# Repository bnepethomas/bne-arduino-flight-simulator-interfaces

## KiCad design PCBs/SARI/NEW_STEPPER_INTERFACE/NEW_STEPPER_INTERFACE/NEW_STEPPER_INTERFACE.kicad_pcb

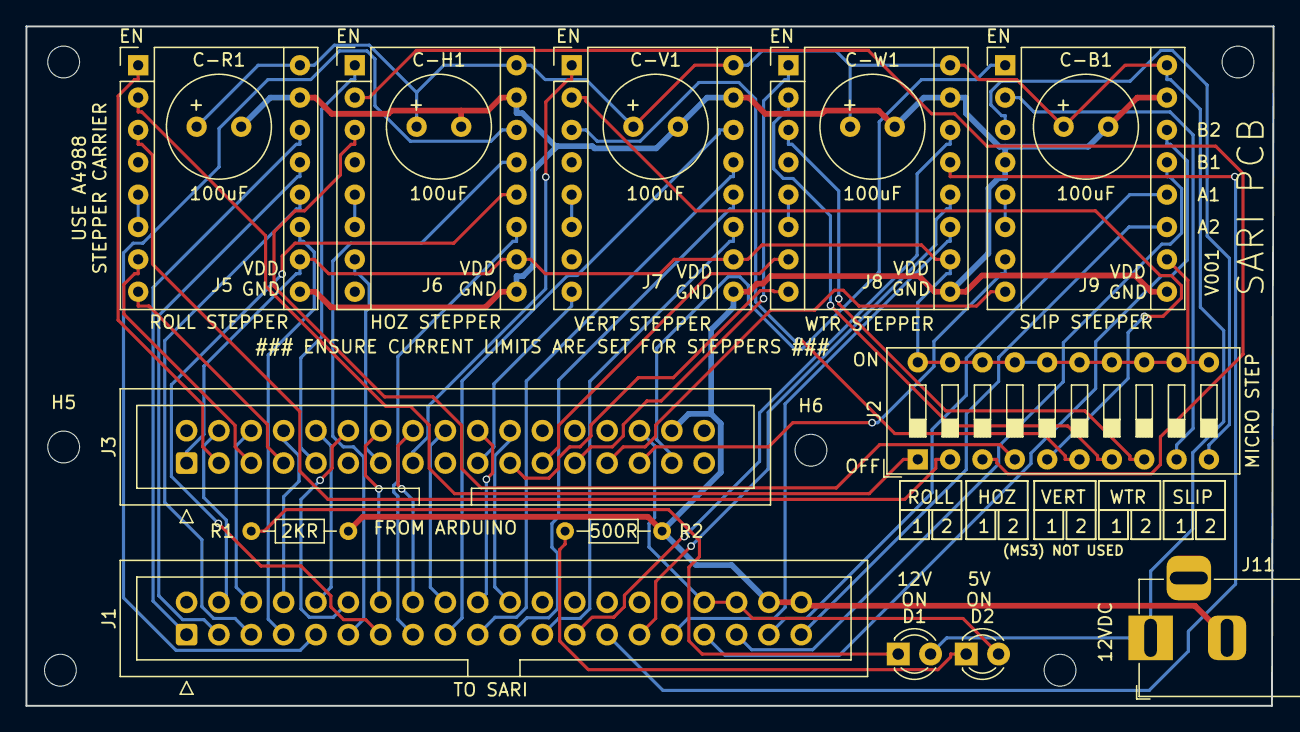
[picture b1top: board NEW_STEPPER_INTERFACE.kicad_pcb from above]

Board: 2 copper layers, 97.9 x 53.3 mm, 24 parts (0 on the bottom side), 64 nets.

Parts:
C-B1: 100uF; C_Radial_D8.0mm_H7.0mm_P3.50mm
C-H1: 100uF; C_Radial_D8.0mm_H7.0mm_P3.50mm
C-R1: 100uF; C_Radial_D8.0mm_H7.0mm_P3.50mm
C-V1: 100uF; C_Radial_D8.0mm_H7.0mm_P3.50mm
C-W1: 100uF; C_Radial_D8.0mm_H7.0mm_P3.50mm
D1, D2: LED; LED_D3.0mm
H1: H1; MountingHole_2.5mm
H2: H2; MountingHole_2.5mm
H3: H3; MountingHole_2.5mm
H4, H5, H6: H4; MountingHole_2.5mm
J1: TO SARI; IDC-Header_2x20_P2.54mm_Vertical
J2: MICRO STEP; SW_DIP_SPSTx10_Slide_9.78x27.58mm_W7.62mm_P2.54mm
J3: FROM ARDUINO; IDC-Header_2x17_P2.54mm_Vertical
J5: ROLL STEPPER; Pololu_Breakout-16_15.2x20.3mm
J6: HOZ STEPPER; Pololu_Breakout-16_15.2x20.3mm
J7: VERT STEPPER; Pololu_Breakout-16_15.2x20.3mm
J8: WTR STEPPER; Pololu_Breakout-16_15.2x20.3mm
J9: SLIP STEPPER; Pololu_Breakout-16_15.2x20.3mm
J11: STEPPER IN 12-20VDC; BarrelJack_Horizontal
R1, R2: R; R_Axial_DIN0204_L3.6mm_D1.6mm_P7.62mm_Horizontal

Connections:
/5VDC: D2.2 (A), J1.34, J1.36, J3.30
/BALL_1A: J1.35, J9.13
/BALL_1B: J1.33, J9.14
/BALL_2A: J1.37, J9.12
/BALL_2B: J1.39, J9.11
/BALL_DIR: J3.27, J9.8
/BALL_EN: J3.31, J9.1
/BALL_MS1: J2.9, J9.2
/BALL_MS2: J2.10, J9.3
/BALL_STEP: J3.29, J9.7
/BALL_STEP_V+: C-B1.1, C-H1.1, C-R1.1, C-V1.1, C-W1.1, D1.2 (A), J5.16, J6.16, J7.16, J8.16, J9.16, J11.1
/ENCODER_A: J1.16, J3.16
/ENCODER_B: J1.18, J3.18
/ENCODER_PUSH: J1.20, J3.20
/HOZ_1A: J1.11, J6.13
/HOZ_1B: J1.9, J6.14
/HOZ_2A: J1.13, J6.12
/HOZ_2B: J1.15, J6.11
/HOZ_EN: J3.9, J6.1
/HOZ_MS1: J2.3, J6.2
/HOZ_MS2: J2.4, J6.3
/HOZ_STEP: J3.13, J6.7
/LED_DATA_IN: J1.12, J3.12
/LED_DATA_OUT: J1.14, J3.14
/ROLL_1A: J1.3, J5.13
/ROLL_1B: J1.1, J5.14
/ROLL_2A: J1.5, J5.12
/ROLL_2B: J1.7, J5.11
/ROLL_DIR: J3.7, J5.8
/ROLL_EN: J3.3, J5.1
/ROLL_MS1: J2.1, J5.2
/ROLL_MS2: J2.2, J5.3
/ROLL_STEP: J3.5, J5.7
/SERVO_FLAG: J1.10, J3.10
/SERVO_PITCH: J1.6, J3.6
/SERVO_RATE: J1.8, J3.8
/TEST_PUSH: J1.22, J3.22
/VDD: J2.11, J2.12, J2.13, J2.14, J2.15, J2.16, J2.17, J2.18, J2.19, J2.20, J3.1, J5.10, J6.10, J7.10, J8.10, J9.10
/VER_1A: J1.19, J7.13
/VER_1B: J1.17, J7.14
/VER_2A: J1.21, J7.12
/VER_2B: J1.23, J7.11
/VER_DIR: J3.19, J7.8
/VER_EN: J3.15, J7.1
/VER_MS1: J2.5, J7.2
/VER_MS2: J2.6, J7.3
/WL_1A: J1.27, J8.13
/WL_1B: J1.25, J8.14
/WL_2A: J1.29, J8.12
/WL_2B: J1.31, J8.11
/WL_DIR: J3.21, J8.8
/WL_EN: J3.25, J8.1
/WL_MS1: J2.7, J8.2
/WL_MS2: J2.8, J8.3
/WL_STEP: J3.23, J8.7
/ZERO_IR: J1.4, J3.4
GNDD: C-B1.2, C-H1.2, C-R1.2, C-V1.2, C-W1.2, J1.38, J1.40, J3.32, J5.9, J5.15, J6.9, J6.15, J7.9, J7.15, J8.9, J8.15, J9.4, J9.9, J9.15, J11.2, R1.1, R2.1
unnamed: D1.1 (K), R1.2
unnamed: D2.1 (K), R2.2
unnamed: J5.5, J5.6
unnamed: J6.5, J6.6
unnamed: J7.5, J7.6
unnamed: J8.5, J8.6
unnamed: J9.5, J9.6

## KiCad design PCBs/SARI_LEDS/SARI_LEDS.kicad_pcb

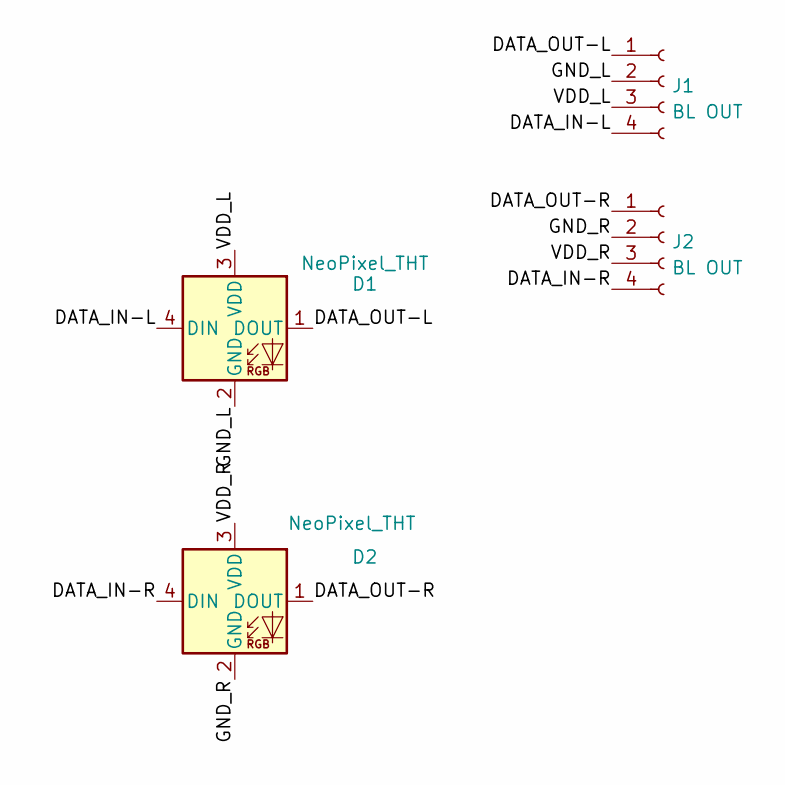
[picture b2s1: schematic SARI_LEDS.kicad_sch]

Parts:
D1, D2: NeoPixel_THT; LED_D5.0mm-4_RGB
J1, J2: BL OUT; PinHeader_1x04_P1.27mm_Vertical

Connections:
/DATA_IN-L: D1.4 (DIN), J1.4
/DATA_IN-R: D2.4 (DIN), J2.4
/DATA_OUT-L: D1.1 (DOUT), J1.1
/DATA_OUT-R: D2.1 (DOUT), J2.1
/GND_L: D1.2 (GND), J1.2
/GND_R: D2.2 (GND), J2.2
/VDD_L: D1.3 (VDD), J1.3
/VDD_R: D2.3 (VDD), J2.3

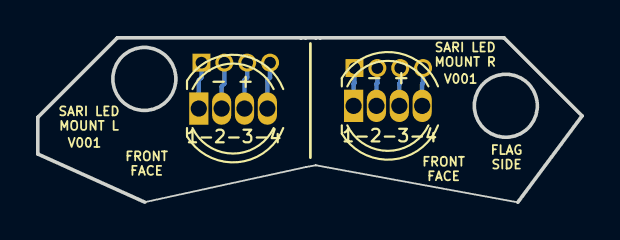
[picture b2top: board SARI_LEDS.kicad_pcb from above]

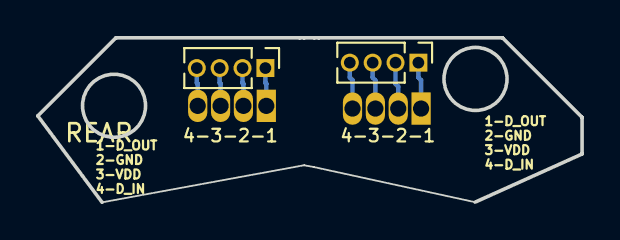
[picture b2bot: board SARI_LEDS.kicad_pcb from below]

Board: 2 copper layers, 30.2 x 9.1 mm, 4 parts (2 on the bottom side), 8 nets.

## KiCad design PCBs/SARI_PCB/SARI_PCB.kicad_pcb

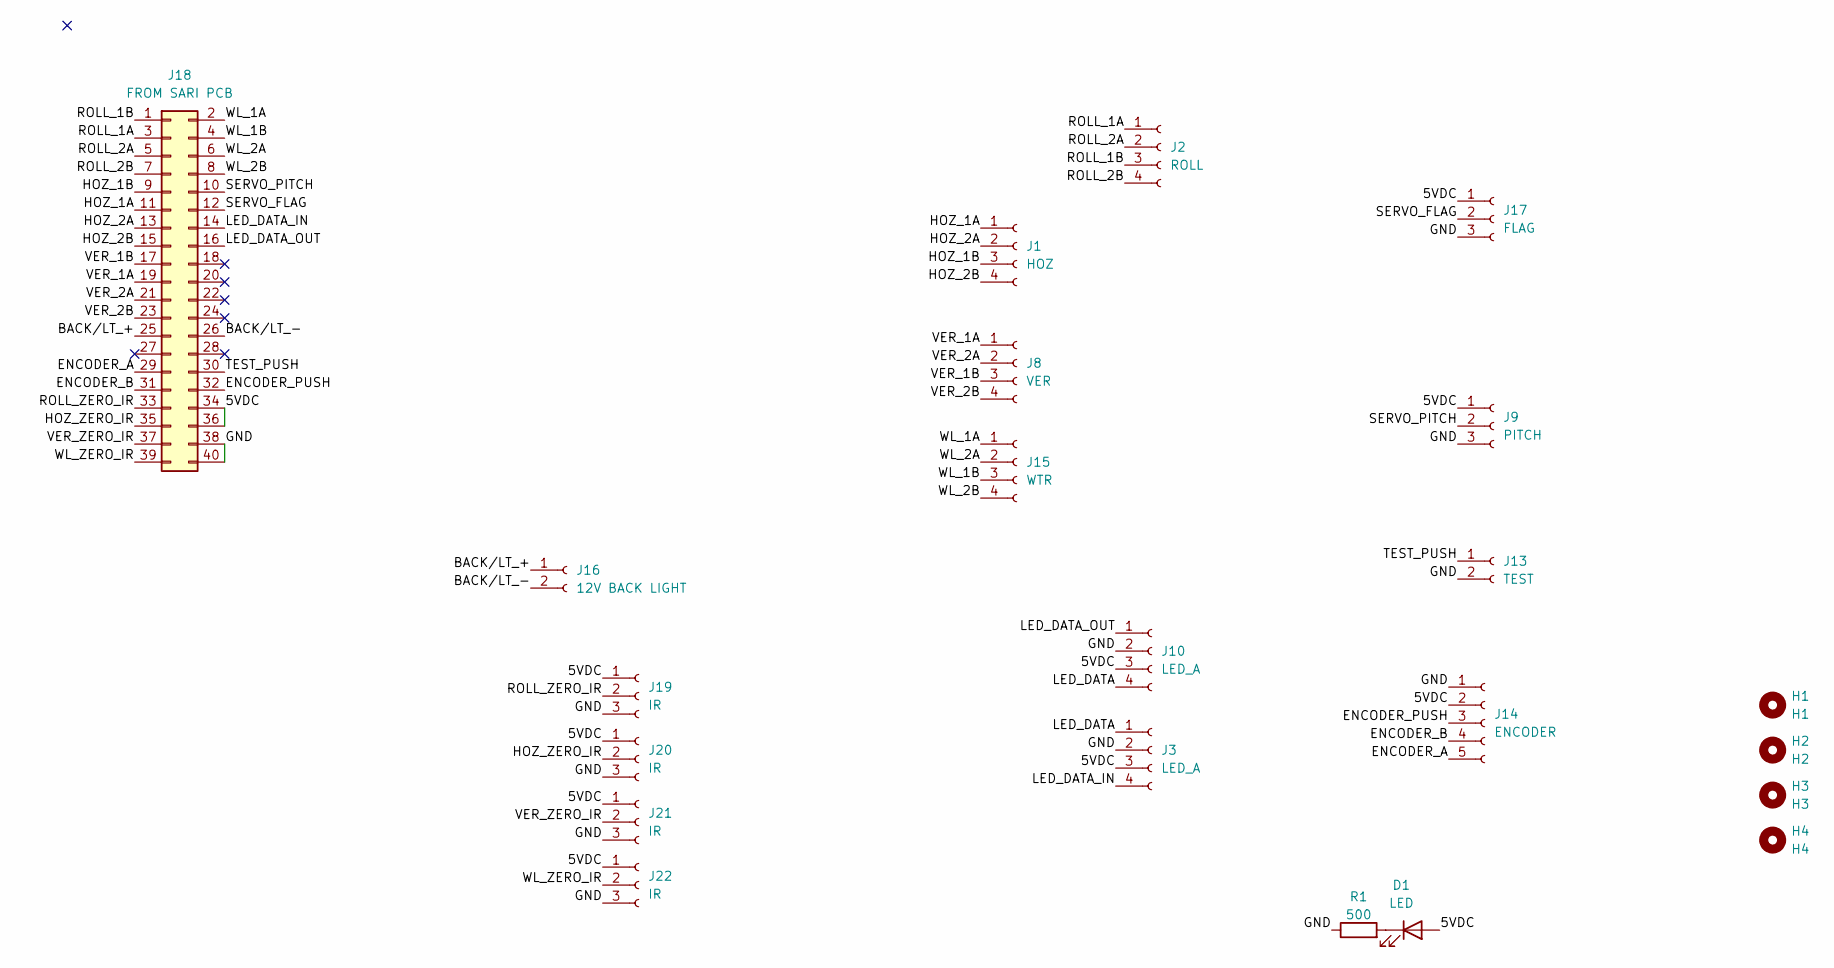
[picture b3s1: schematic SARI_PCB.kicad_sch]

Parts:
D1: LED; LED_D3.0mm
H1: H1; MountingHole_2.5mm
H2: H2; MountingHole_2.5mm
H3: H3; MountingHole_2.5mm
H4: H4; MountingHole_2.5mm
J1: HOZ; Molex_PicoBlade_53047-0410_1x04_P1.25mm_Vertical
J2: ROLL; JST_XH_B4B-XH-A_1x04_P2.50mm_Vertical
J3, J10: LED_A; Molex_PicoBlade_53047-0410_1x04_P1.25mm_Vertical
J8: VER; Molex_PicoBlade_53047-0410_1x04_P1.25mm_Vertical
J9: PITCH; JST_XH_B3B-XH-A_1x03_P2.50mm_Vertical
J13: TEST; JST_XH_B2B-XH-A_1x02_P2.50mm_Vertical
J14: ENCODER; JST_XH_B5B-XH-A_1x05_P2.50mm_Vertical
J15: WTR; Molex_PicoBlade_53047-0410_1x04_P1.25mm_Vertical
J16: 12V BACK LIGHT; JST_XH_B2B-XH-A_1x02_P2.50mm_Vertical
J17: FLAG; Molex_PicoBlade_53047-0310_1x03_P1.25mm_Vertical
J18: FROM SARI PCB; IDC-Header_2x20_P2.54mm_Vertical
J19, J20, J21, J22: IR; Molex_PicoBlade_53047-0310_1x03_P1.25mm_Vertical
R1: 500; R_Axial_DIN0207_L6.3mm_D2.5mm_P7.62mm_Horizontal

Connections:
/5VDC: D1.2 (A), J3.3, J9.1, J10.3, J14.2, J17.1, J18.34, J18.36, J19.1, J20.1, J21.1, J22.1
/BACK/LT_+: J16.1, J18.25
/BACK/LT_-: J16.2, J18.26
/ENCODER_A: J14.5, J18.29
/ENCODER_B: J14.4, J18.31
/ENCODER_PUSH: J14.3, J18.32
/GND: J3.2, J9.3, J10.2, J13.2, J14.1, J17.3, J18.38, J18.40, J19.3, J20.3, J21.3, J22.3, R1.1
/HOZ_1A: J1.1, J18.11
/HOZ_1B: J1.3, J18.9
/HOZ_2A: J1.2, J18.13
/HOZ_2B: J1.4, J18.15
/HOZ_ZERO_IR: J18.35, J20.2
/LED_DATA: J3.1, J10.4
/LED_DATA_IN: J3.4, J18.14
/LED_DATA_OUT: J10.1, J18.16
/ROLL_1A: J2.1, J18.3
/ROLL_1B: J2.3, J18.1
/ROLL_2A: J2.2, J18.5
/ROLL_2B: J2.4, J18.7
/ROLL_ZERO_IR: J18.33, J19.2
/SERVO_FLAG: J17.2, J18.12
/SERVO_PITCH: J9.2, J18.10
/TEST_PUSH: J13.1, J18.30
/VER_1A: J8.1, J18.19
/VER_1B: J8.3, J18.17
/VER_2A: J8.2, J18.21
/VER_2B: J8.4, J18.23
/VER_ZERO_IR: J18.37, J21.2
/WL_1A: J15.1, J18.2
/WL_1B: J15.3, J18.4
/WL_2A: J15.2, J18.6
/WL_2B: J15.4, J18.8
/WL_ZERO_IR: J18.39, J22.2
unnamed: D1.1 (K), R1.2

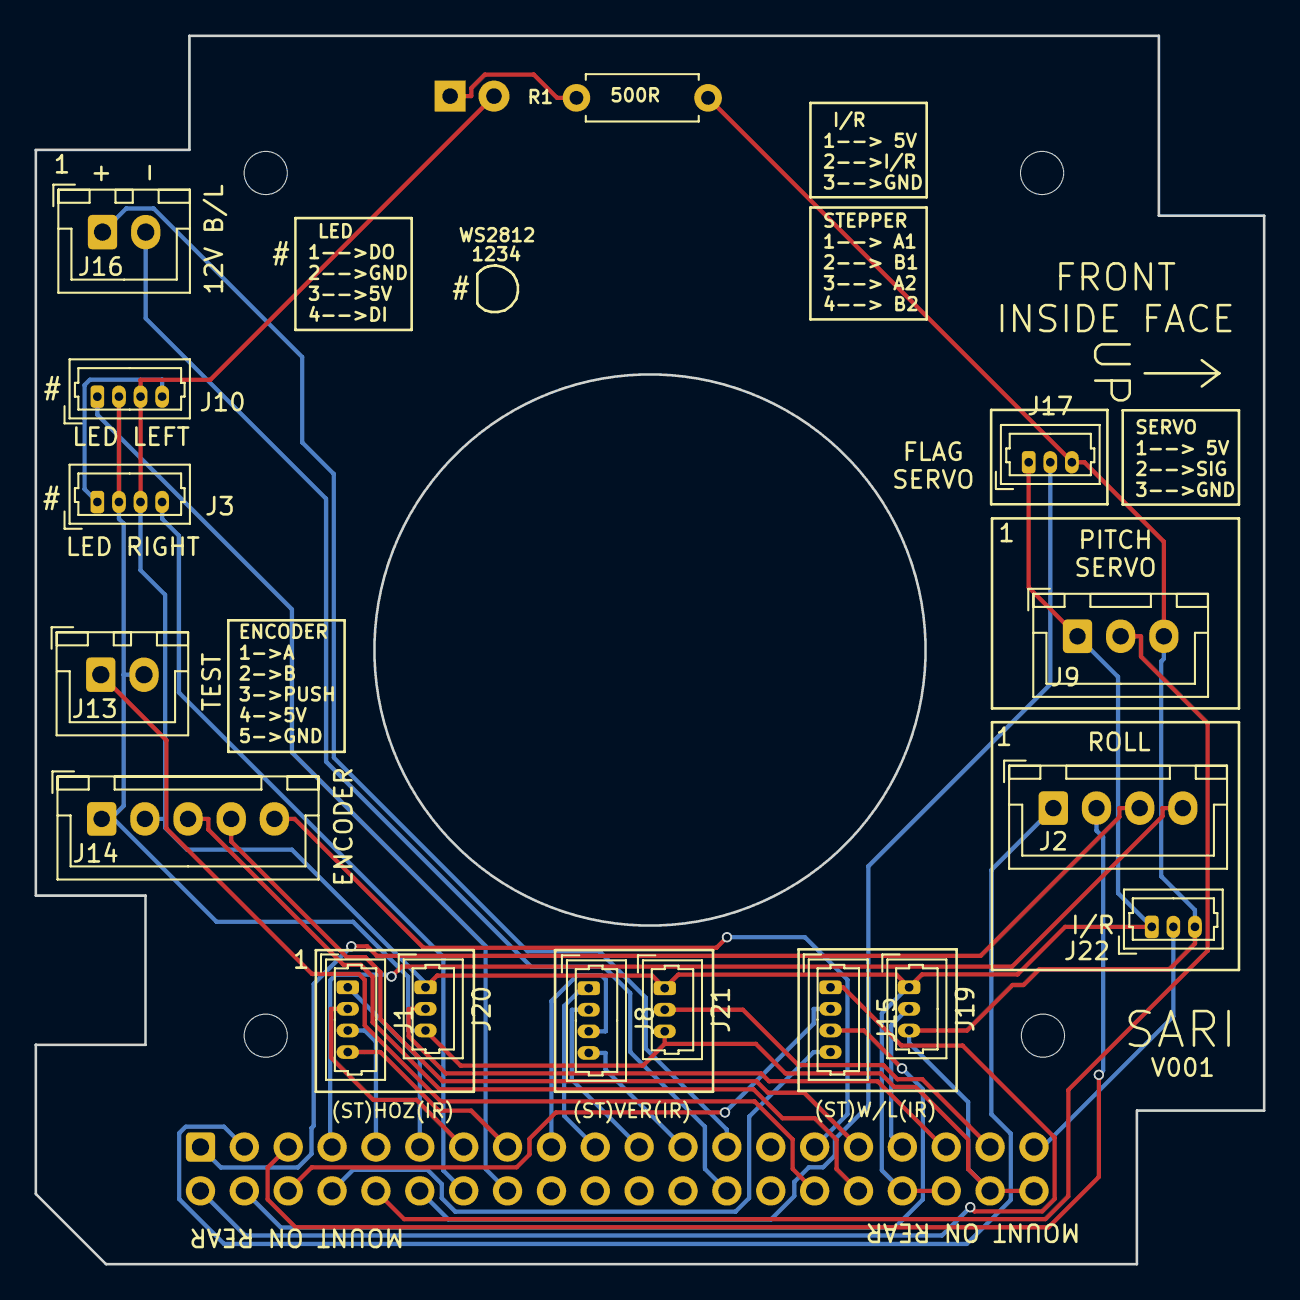
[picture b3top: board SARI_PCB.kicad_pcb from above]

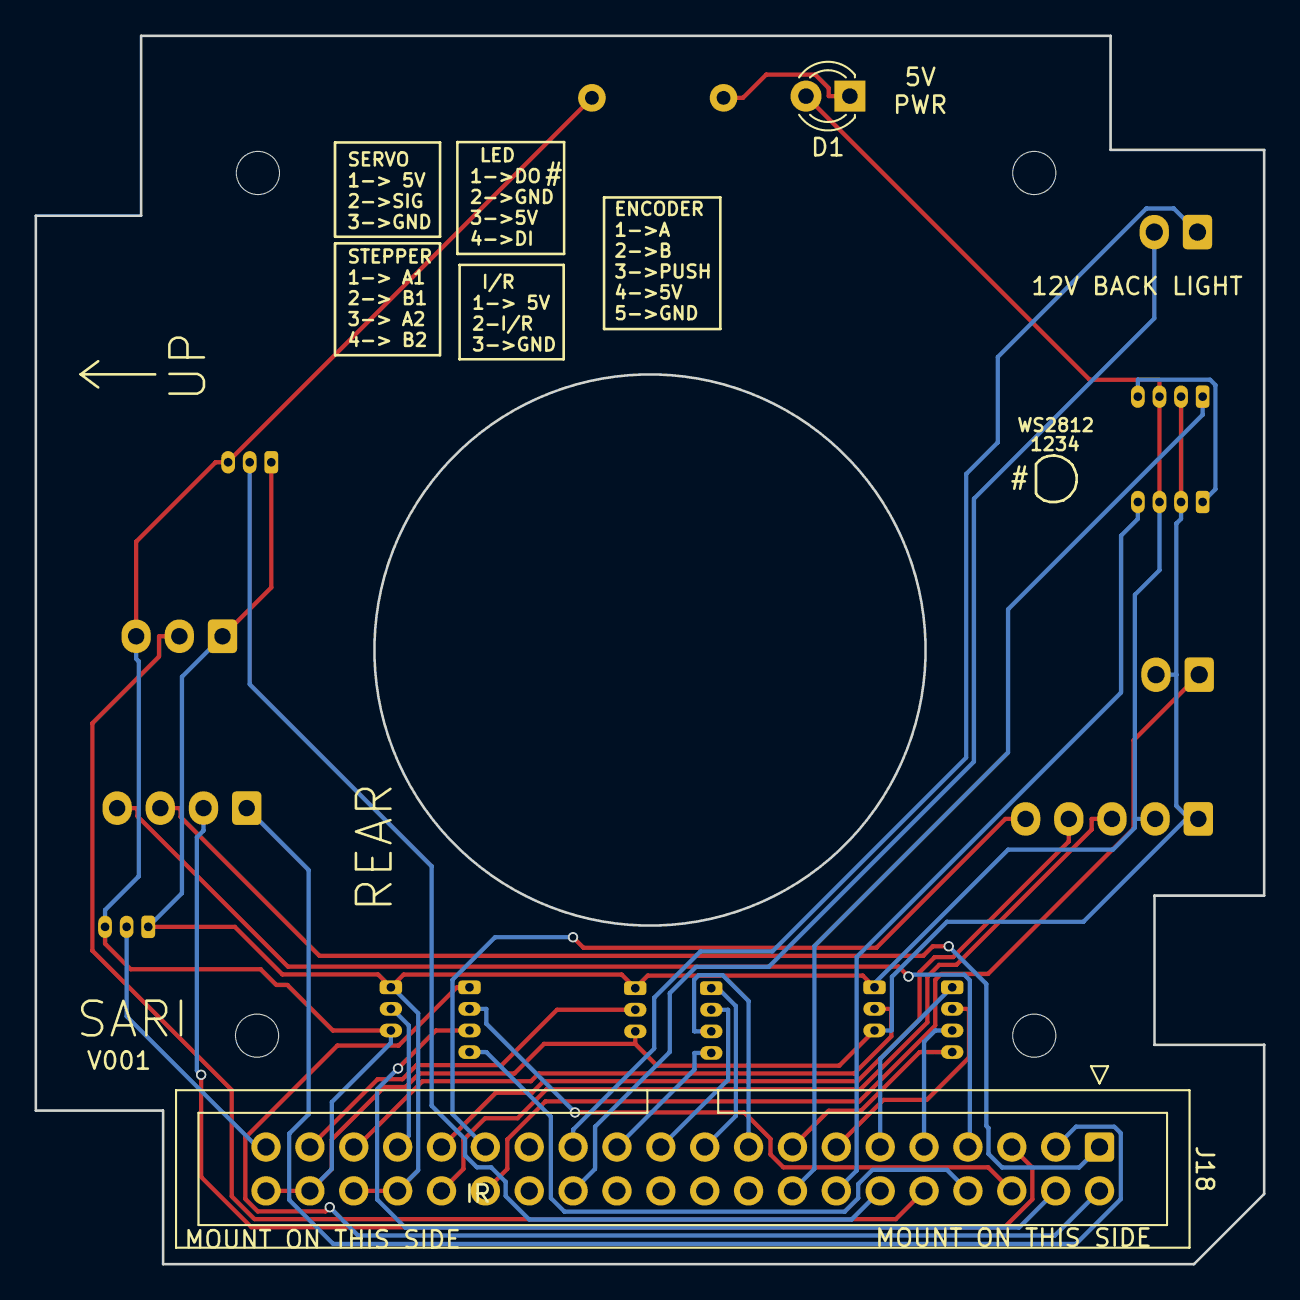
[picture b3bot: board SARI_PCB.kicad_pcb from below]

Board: 2 copper layers, 71.1 x 71.1 mm, 22 parts (2 on the bottom side), 34 nets.

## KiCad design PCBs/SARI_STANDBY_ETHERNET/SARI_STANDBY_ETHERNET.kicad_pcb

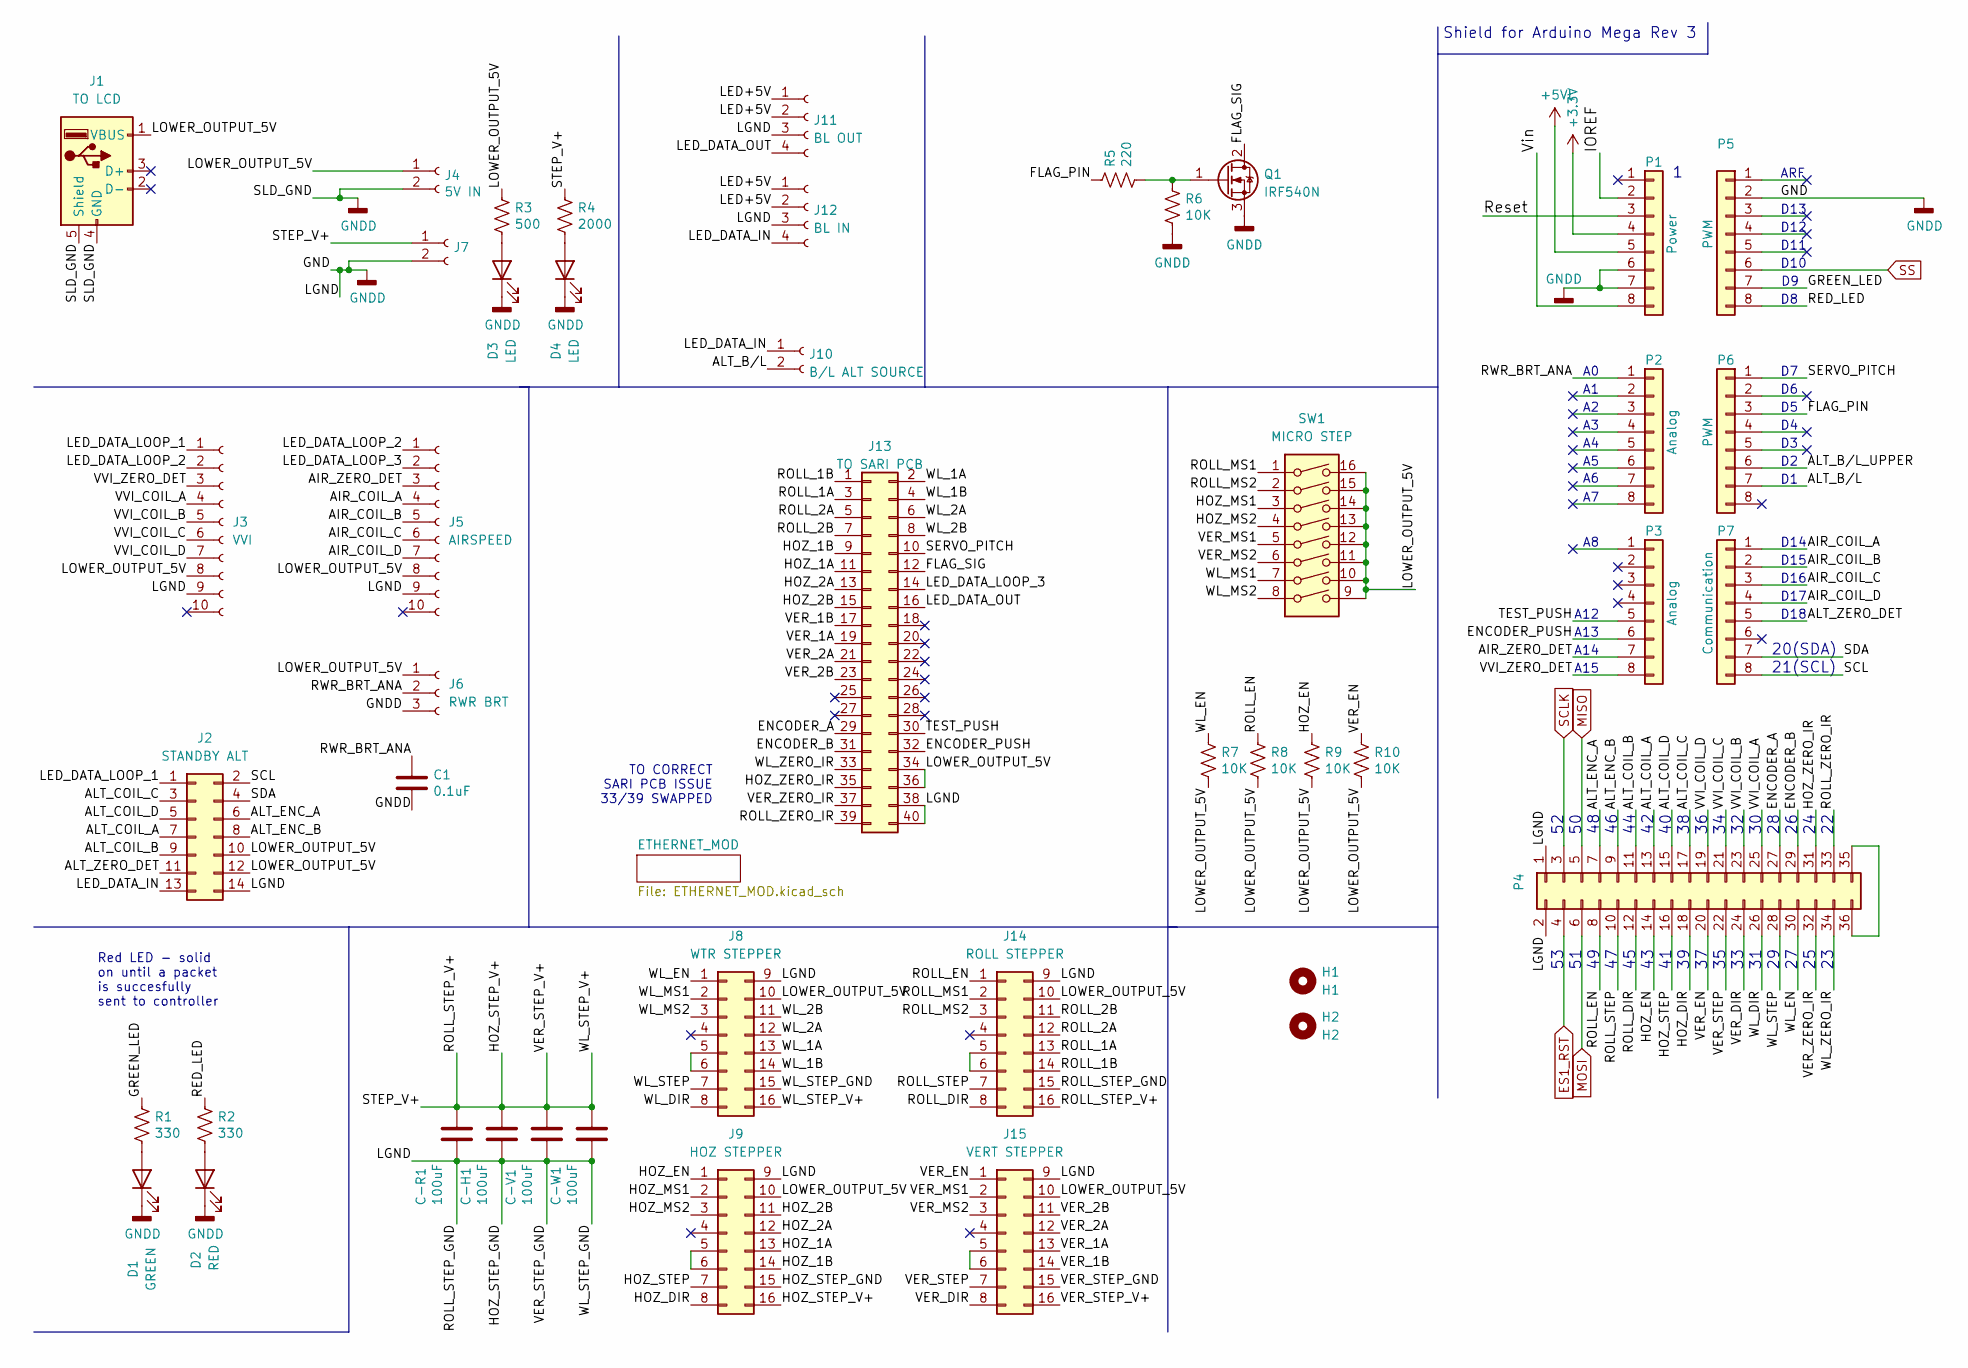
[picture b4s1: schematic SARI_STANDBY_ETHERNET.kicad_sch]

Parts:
C1: 0.1uF; C_Disc_D6.0mm_W2.5mm_P5.00mm
C-H1: 100uF; C_Radial_D8.0mm_H7.0mm_P3.50mm
C-R1: 100uF; C_Radial_D8.0mm_H7.0mm_P3.50mm
C-V1: 100uF; C_Radial_D8.0mm_H7.0mm_P3.50mm
C-W1: 100uF; C_Radial_D8.0mm_H7.0mm_P3.50mm
D1: GREEN; LED_D3.0mm
D2: RED; LED_D3.0mm
D3, D4: LED; LED_D3.0mm
H1: H1; MountingHole_2.5mm
H2: H2; MountingHole_2.5mm
J1: TO LCD; USB_A_Molex_67643_Horizontal
J2: STANDBY ALT; IDC-Header_2x07_P2.54mm_Vertical
J3: VVI; JST_XH_B10B-XH-A_1x10_P2.50mm_Vertical
J4: 5V IN; BarrelJack_Horizontal
J5: AIRSPEED; JST_XH_B10B-XH-A_1x10_P2.50mm_Vertical
J6: RWR BRT; JST_XH_B3B-XH-A_1x03_P2.50mm_Vertical
J7: STEPPER IN 12-20VDC; BarrelJack_Horizontal
J8: WTR STEPPER; Pololu_Breakout-16_15.2x20.3mm
J9: HOZ STEPPER; Pololu_Breakout-16_15.2x20.3mm
J10: B/L ALT SOURCE; PinHeader_1x02_P2.54mm_Vertical
J11: BL OUT; Molex_Mini-Fit_Jr_5566-04A_2x02_P4.20mm_Vertical
J12: BL IN; Molex_Mini-Fit_Jr_5566-04A_2x02_P4.20mm_Vertical
J13: TO SARI PCB; IDC-Header_2x20_P2.54mm_Vertical
J14: ROLL STEPPER; Pololu_Breakout-16_15.2x20.3mm
J15: VERT STEPPER; Pololu_Breakout-16_15.2x20.3mm
P1: Power; Socket_Strip_Arduino_1x08
P2, P3: Analog; Socket_Strip_Arduino_1x08
P4: Digital; Socket_Strip_Arduino_2x18
P5, P6: PWM; Socket_Strip_Arduino_1x08
P7: Communication; Socket_Strip_Arduino_1x08
Q1: IRF540N; TO-220-3_Vertical
R1: 330; R_Axial_DIN0204_L3.6mm_D1.6mm_P2.54mm_Vertical
R2: 330; PT_R_Axial_DIN0204_L3.6mm_D1.6mm_P2.54mm_Vertical
R3: 500; R_Axial_DIN0204_L3.6mm_D1.6mm_P2.54mm_Vertical
R4: 2000; R_Axial_DIN0204_L3.6mm_D1.6mm_P2.54mm_Vertical
R5: 220; R_Axial_DIN0204_L3.6mm_D1.6mm_P2.54mm_Vertical
R6, R7, R8, R9, R10: 10K; R_Axial_DIN0204_L3.6mm_D1.6mm_P2.54mm_Vertical
SW1: MICRO STEP; SW_DIP_SPSTx08_Slide_9.78x22.5mm_W7.62mm_P2.54mm

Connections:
+5VL: P1.5
/AIR_COIL_A: J5.4, P7.1
/AIR_COIL_B: J5.5, P7.2
/AIR_COIL_C: J5.6, P7.3
/AIR_COIL_D: J5.7, P7.4
/AIR_ZERO_DET: J5.3, P3.7
/ALT_B/L: J10.2, P6.7
/ALT_B/L_UPPER: P6.6
/ALT_COIL_A: J2.7, P4.13
/ALT_COIL_B: J2.9, P4.11
/ALT_COIL_C: J2.3, P4.17
/ALT_COIL_D: J2.5, P4.15
/ALT_ENC_A: J2.6, P4.7
/ALT_ENC_B: J2.8, P4.9
/ALT_ZERO_DET: J2.11, P7.5
/ENCODER_A: J13.29, P4.27
/ENCODER_B: J13.31, P4.29
/ENCODER_PUSH: J13.32, P3.6
/FLAG_PIN: P6.3, R5.1
/FLAG_SIG: J13.12, Q1.2 (D)
/GREEN_LED: P5.7, R1.1
/HOZ_1A: J9.13, J13.11
/HOZ_1B: J9.14, J13.9
/HOZ_2A: J9.12, J13.13
/HOZ_2B: J9.11, J13.15
/HOZ_DIR: J9.8, P4.18
/HOZ_EN: J9.1, P4.14, R9.1
/HOZ_MS1: J9.2, SW1.3
/HOZ_MS2: J9.3, SW1.4
/HOZ_STEP: J9.7, P4.16
/HOZ_STEP_V+: C-H1.1, C-R1.1, C-V1.1, C-W1.1, J7.1, J8.16, J9.16, J14.16, J15.16, R4.1
/HOZ_ZERO_IR: J13.35, P4.31
/IOREF: P1.2
/LED+5V: J11.1, J11.2, J12.1, J12.2
/LED_DATA_IN: J2.13, J10.1, J12.4
/LED_DATA_LOOP_1: J2.1, J3.1
/LED_DATA_LOOP_2: J3.2, J5.1
/LED_DATA_LOOP_3: J5.2, J13.14
/LED_DATA_OUT: J11.4, J13.16
/LOWER_OUTPUT_5V: J1.1 (VBUS), J2.10, J2.12, J3.8, J4.1, J5.8, J6.1, J8.10, J9.10, J13.34, J13.36, J14.10, J15.10, R3.1, R7.2, R8.2, R9.2, R10.2, SW1.9, SW1.10, SW1.11, SW1.12, SW1.13, SW1.14, SW1.15, SW1.16
/RED_LED: P5.8, R2.1
/ROLL_1A: J13.3, J14.13
/ROLL_1B: J13.1, J14.14
/ROLL_2A: J13.5, J14.12
/ROLL_2B: J13.7, J14.11
/ROLL_DIR: J14.8, P4.12
/ROLL_EN: J14.1, P4.8, R8.1
/ROLL_MS1: J14.2, SW1.1
/ROLL_MS2: J14.3, SW1.2
/ROLL_STEP: J14.7, P4.10
/ROLL_ZERO_IR: J13.39, P4.33
/RWR_BRT_ANA: C1.1, J6.2, P2.1
/Reset: P1.3
/SCL: J2.2, P7.8
/SDA: J2.4, P7.7
/SERVO_PITCH: J13.10, P6.1
/TEST_PUSH: J13.30, P3.5
/VER_1A: J13.19, J15.13
/VER_1B: J13.17, J15.14
/VER_2A: J13.21, J15.12
/VER_2B: J13.23, J15.11
/VER_DIR: J15.8, P4.24
/VER_EN: J15.1, P4.20, R10.1
/VER_MS1: J15.2, SW1.5
/VER_MS2: J15.3, SW1.6
/VER_STEP: J15.7, P4.22
/VER_ZERO_IR: J13.37, P4.32
/VVI_COIL_A: J3.4, P4.25
/VVI_COIL_B: J3.5, P4.23
/VVI_COIL_C: J3.6, P4.21
/VVI_COIL_D: J3.7, P4.19
/VVI_ZERO_DET: J3.3, P3.8
/Vin: P1.8
/WL_1A: J8.13, J13.2
/WL_1B: J8.14, J13.4
/WL_2A: J8.12, J13.6
/WL_2B: J8.11, J13.8
/WL_DIR: J8.8, P4.26
/WL_EN: J8.1, P4.30, R7.1
/WL_MS1: J8.2, SW1.7
/WL_MS2: J8.3, SW1.8
/WL_STEP: J8.7, P4.28
/WL_ZERO_IR: J13.33, P4.34
ES1_RST: P4.4; also elsewhere on the board
MISO: P4.5; also elsewhere on the board
MOSI: P4.6; also elsewhere on the board
unnamed: D1.2 (A), R1.2
unnamed: D2.2 (A), R2.2
unnamed: D3.2 (A), R3.2
unnamed: D4.2 (A), R4.2
unnamed: J8.5, J8.6
unnamed: J9.5, J9.6
unnamed: J14.5, J14.6
unnamed: J15.5, J15.6
unnamed: P4.35, P4.36
unnamed: Q1.1 (G), R5.2, R6.1
SCLK: P4.3; also elsewhere on the board
SS: P5.6; also elsewhere on the board

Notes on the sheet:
A14
ARF
Shield for Arduino Mega Rev 3
D10
TO CORRECT SARI PCB ISSUE 33/39 SWAPPED
D13
Red LED - solid on until a packet is succesfully sent to controller
A13
A12
D14
A15
D15
D12
D17
D11
20(SDA)
21(SCL)
D16
D18

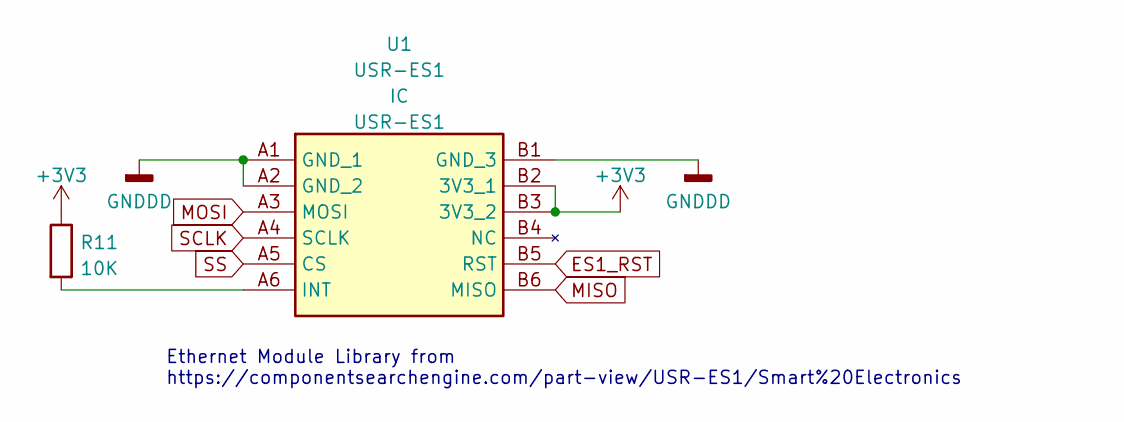
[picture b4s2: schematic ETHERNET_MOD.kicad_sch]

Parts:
R11: 10K; PT_R_Axial_DIN0204_L3.6mm_D1.6mm_P2.54mm_Vertical
U1: USR-ES1; USRES1; Manufacturer_Part_Number USR-ES1

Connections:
ES1_RST: U1.B5 (RST); also elsewhere on the board
MISO: U1.B6 (MISO); also elsewhere on the board
MOSI: U1.A3 (MOSI); also elsewhere on the board
unnamed: R11.2, U1.A6 (INT)
SCLK: U1.A4 (SCLK); also elsewhere on the board
SS: U1.A5 (CS); also elsewhere on the board

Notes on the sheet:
Ethernet Module Library from https://componentsearchengine.com/part-view/USR-ES1/Smart%20Electronics

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
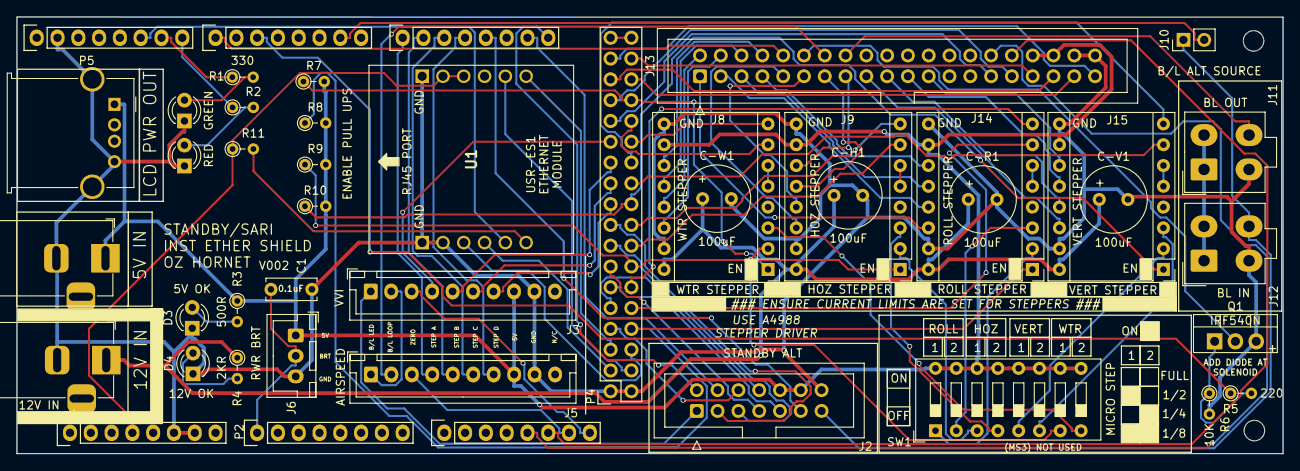
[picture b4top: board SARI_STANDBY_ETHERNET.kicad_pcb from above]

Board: 2 copper layers, 154.7 x 53.3 mm, 47 parts (0 on the bottom side), 96 nets.

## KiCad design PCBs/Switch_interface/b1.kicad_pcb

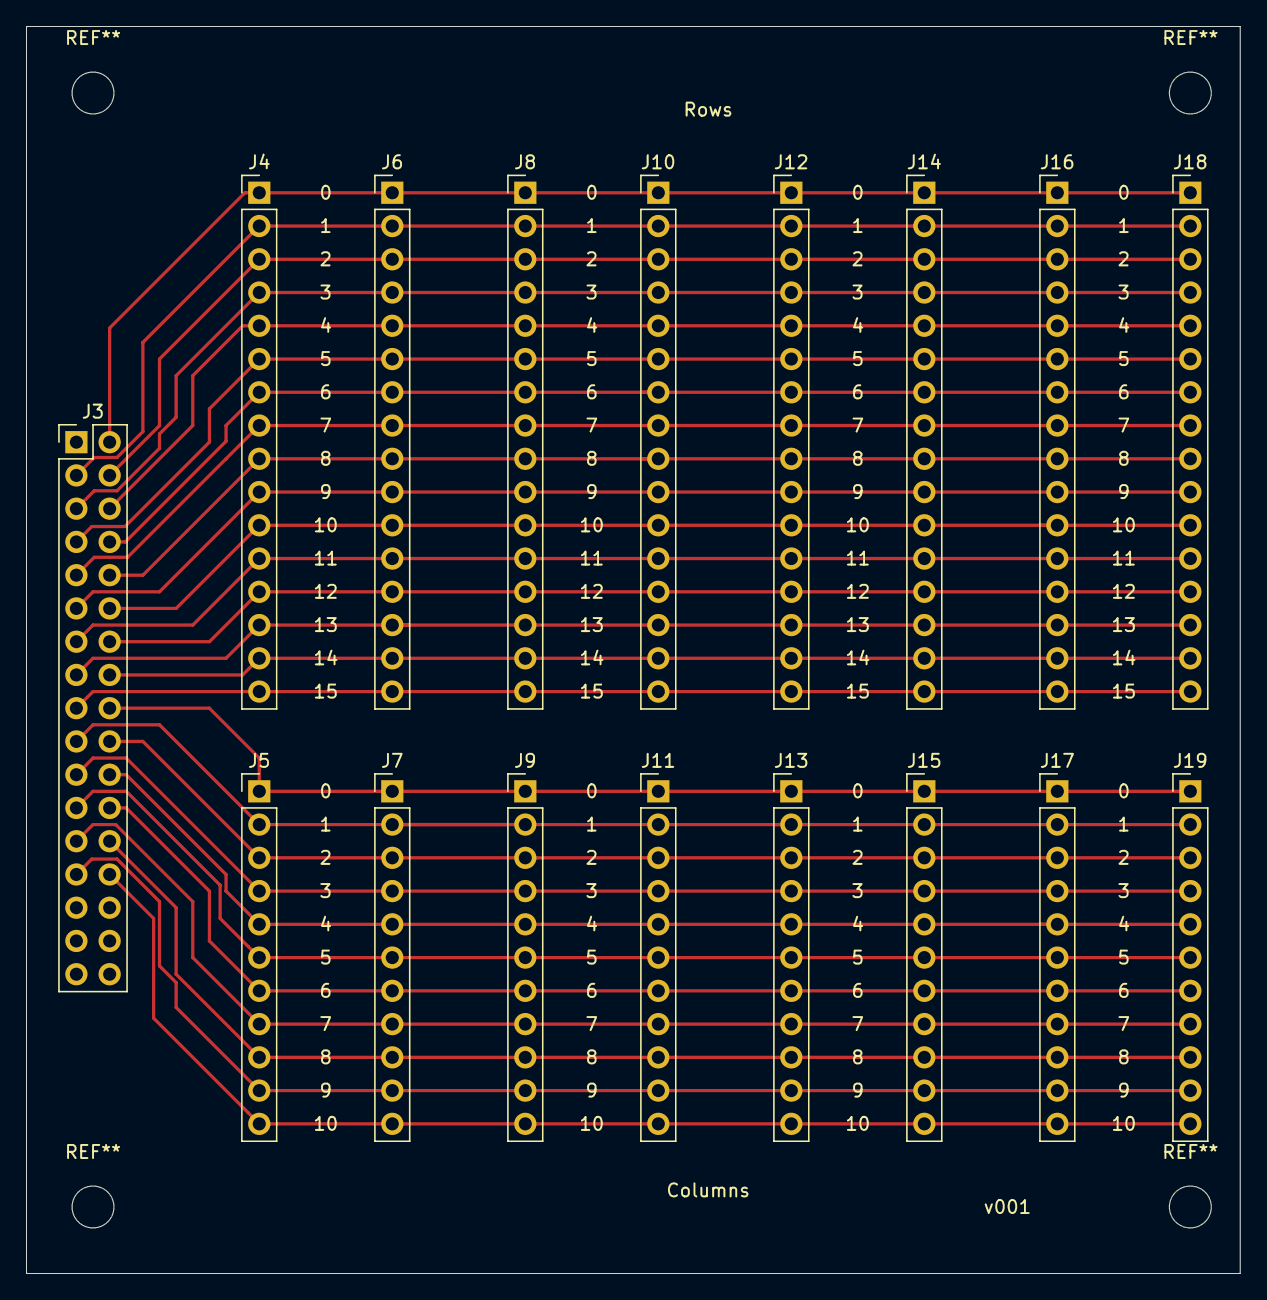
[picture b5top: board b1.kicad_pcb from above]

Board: 2 copper layers, 92.7 x 95.2 mm, 17 parts (0 on the bottom side), 27 nets.

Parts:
J3: PinHeader_2x17_P2.54mm_Vertical
J4, J6, J8, J10, J12, J14, J16, J18: PinHeader_1x16_P2.54mm_Vertical
J5, J7, J9, J11, J13, J15, J17, J19: PinHeader_1x11_P2.54mm_Vertical

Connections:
/Col0: J3.18, J5.1, J7.1, J9.1, J11.1, J13.1, J15.1, J17.1, J19.1
/Col1: J3.19, J5.2, J7.2, J9.2, J11.2, J13.2, J15.2, J17.2, J19.2
/Col2: J3.20, J5.3, J7.3, J9.3, J11.3, J13.3, J15.3, J17.3, J19.3
/Col3: J3.21, J5.4, J7.4, J9.4, J11.4, J13.4, J15.4, J17.4, J19.4
/Col4: J3.22, J5.5, J7.5, J9.5, J11.5, J13.5, J15.5, J17.5, J19.5
/Col5: J3.23, J5.6, J7.6, J9.6, J11.6, J13.6, J15.6, J17.6, J19.6
/Col6: J3.24, J5.7, J7.7, J9.7, J11.7, J13.7, J15.7, J17.7, J19.7
/Col7: J3.25, J5.8, J7.8, J9.8, J11.8, J13.8, J15.8, J17.8, J19.8
/Col8: J3.26, J5.9, J7.9, J9.9, J11.9, J13.9, J15.9, J17.9, J19.9
/Col9: J3.27, J5.10, J7.10, J9.10, J11.10, J13.10, J15.10, J17.10, J19.10
/Col10: J3.28, J5.11, J7.11, J9.11, J11.11, J13.11, J15.11, J17.11, J19.11
/Row0: J3.2, J4.1, J6.1, J8.1, J10.1, J12.1, J14.1, J16.1, J18.1
/Row1: J3.3, J4.2, J6.2, J8.2, J10.2, J12.2, J14.2, J16.2, J18.2
/Row2: J3.4, J4.3, J6.3, J8.3, J10.3, J12.3, J14.3, J16.3, J18.3
/Row3: J3.5, J4.4, J6.4, J8.4, J10.4, J12.4, J14.4, J16.4, J18.4
/Row4: J3.6, J4.5, J6.5, J8.5, J10.5, J12.5, J14.5, J16.5, J18.5
/Row5: J3.7, J4.6, J6.6, J8.6, J10.6, J12.6, J14.6, J16.6, J18.6
/Row6: J3.8, J4.7, J6.7, J8.7, J10.7, J12.7, J14.7, J16.7, J18.7
/Row7: J3.9, J4.8, J6.8, J8.8, J10.8, J12.8, J14.8, J16.8, J18.8
/Row8: J3.10, J4.9, J6.9, J8.9, J10.9, J12.9, J14.9, J16.9, J18.9
/Row9: J3.11, J4.10, J6.10, J8.10, J10.10, J12.10, J14.10, J16.10, J18.10
/Row10: J3.12, J4.11, J6.11, J8.11, J10.11, J12.11, J14.11, J16.11, J18.11
/Row11: J3.13, J4.12, J6.12, J8.12, J10.12, J12.12, J14.12, J16.12, J18.12
/Row12: J3.14, J4.13, J6.13, J8.13, J10.13, J12.13, J14.13, J16.13, J18.13
/Row13: J3.15, J4.14, J6.14, J8.14, J10.14, J12.14, J14.14, J16.14, J18.14
/Row14: J3.16, J4.15, J6.15, J8.15, J10.15, J12.15, J14.15, J16.15, J18.15
/Row15: J3.17, J4.16, J6.16, J8.16, J10.16, J12.16, J14.16, J16.16, J18.16

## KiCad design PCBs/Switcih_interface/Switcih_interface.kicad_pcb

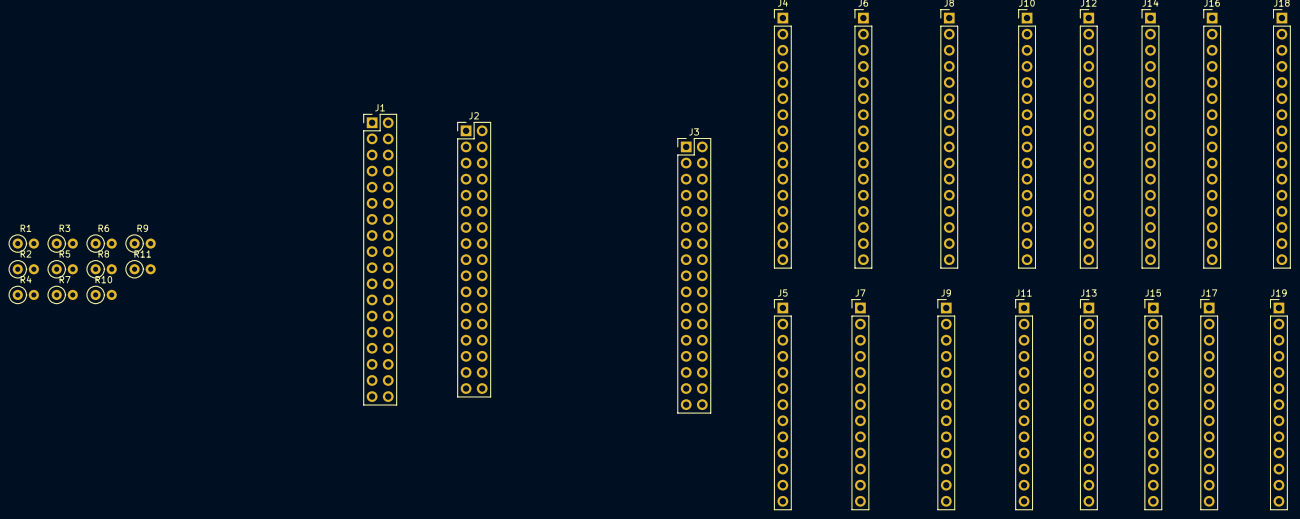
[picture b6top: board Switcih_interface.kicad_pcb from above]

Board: 2 copper layers, 30 parts (0 on the bottom side), 29 nets, no tracks yet.

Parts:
J1: Conn_02x18_Odd_Even; PinHeader_2x18_P2.54mm_Vertical
J2, J3: Conn_02x18_Odd_Even; PinHeader_2x17_P2.54mm_Vertical
J4, J6, J8, J10, J12, J14, J16, J18: Conn_01x13; PinHeader_1x16_P2.54mm_Vertical
J5, J7, J9, J11, J13, J15, J17, J19: Conn_01x13; PinHeader_1x13_P2.54mm_Vertical
R1, R2, R3, R4, R5, R6, R7, R8, R9, R10, R11: R_US; R_Axial_DIN0207_L6.3mm_D2.5mm_P2.54mm_Vertical

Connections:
+5V: J1.1, J1.2, R1.1, R2.1, R3.1, R4.1, R5.1, R6.1, R7.1, R8.1, R9.1, R10.1, R11.1
/Col0: J1.19, J2.18, J3.18, J5.1, J7.1, J9.1, J11.1, J13.1, J15.1, J17.1, J19.1, R11.2
/Col1: J1.20, J2.19, J3.19, J5.2, J7.2, J9.2, J11.2, J13.2, J15.2, J17.2, J19.2, R10.2
/Col2: J1.21, J2.20, J3.20, J5.3, J7.3, J9.3, J11.3, J13.3, J15.3, J17.3, J19.3, R9.2
/Col3: J1.22, J2.21, J3.21, J5.4, J7.4, J9.4, J11.4, J13.4, J15.4, J17.4, J19.4, R8.2
/Col4: J1.23, J2.22, J3.22, J5.5, J7.5, J9.5, J11.5, J13.5, J15.5, J17.5, J19.5, R7.2
/Col5: J1.24, J2.23, J3.23, J5.6, J7.6, J9.6, J11.6, J13.6, J15.6, J17.6, J19.6, R6.2
/Col6: J1.25, J2.24, J3.24, J5.7, J7.7, J9.7, J11.7, J13.7, J15.7, J17.7, J19.7, R5.2
/Col7: J1.26, J2.25, J3.25, J5.8, J7.8, J9.8, J11.8, J13.8, J15.8, J17.8, J19.8, R4.2
/Col8: J1.27, J2.26, J3.26, J5.9, J7.9, J9.9, J11.9, J13.9, J15.9, J17.9, J19.9, R3.2
/Col9: J1.28, J2.27, J3.27, J5.10, J7.10, J9.10, J11.10, J13.10, J15.10, J17.10, J19.10, R2.2
/Col10: J1.29, J2.28, J3.28, J5.11, J7.11, J9.11, J11.11, J13.11, J15.11, J17.11, J19.11, R1.2
/Row0: J1.3, J2.2, J3.2, J4.1, J6.1, J8.1, J10.1, J12.1, J14.1, J16.1, J18.1
/Row1: J1.4, J2.3, J3.3, J4.2, J6.2, J8.2, J10.2, J12.2, J14.2, J16.2, J18.2
/Row2: J1.5, J2.4, J3.4, J4.3, J6.3, J8.3, J10.3, J12.3, J14.3, J16.3, J18.3
/Row3: J1.6, J2.5, J3.5, J4.4, J6.4, J8.4, J10.4, J12.4, J14.4, J16.4, J18.4
/Row4: J1.7, J2.6, J3.6, J4.5, J6.5, J8.5, J10.5, J12.5, J14.5, J16.5, J18.5
/Row5: J1.8, J2.7, J3.7, J4.6, J6.6, J8.6, J10.6, J12.6, J14.6, J16.6, J18.6
/Row6: J1.9, J2.8, J3.8, J4.7, J6.7, J8.7, J10.7, J12.7, J14.7, J16.7, J18.7
/Row7: J1.10, J2.9, J3.9, J4.8, J6.8, J8.8, J10.8, J12.8, J14.8, J16.8, J18.8
/Row8: J1.11, J2.10, J3.10, J4.9, J6.9, J8.9, J10.9, J12.9, J14.9, J16.9, J18.9
/Row9: J1.12, J2.11, J3.11, J4.10, J6.10, J8.10, J10.10, J12.10, J14.10, J16.10, J18.10
/Row10: J1.13, J2.12, J3.12, J4.11, J6.11, J8.11, J10.11, J12.11, J14.11, J16.11, J18.11
/Row11: J1.14, J2.13, J3.13, J4.12, J6.12, J8.12, J10.12, J12.12, J14.12, J16.12, J18.12
/Row12: J1.15, J2.14, J3.14, J4.13, J6.13, J8.13, J10.13, J12.13, J14.13, J16.13, J18.13
/Row13: J1.16, J2.15, J3.15, J4.14, J6.14, J8.14, J10.14, J12.14, J14.14, J16.14, J18.14
/Row14: J1.17, J2.16, J3.16, J4.15, J6.15, J8.15, J10.15, J12.15, J14.15, J16.15, J18.15
/Row15: J1.18, J2.17, J3.17, J4.16, J6.16, J8.16, J10.16, J12.16, J14.16, J16.16, J18.16
unnamed: J1.35, J1.36
